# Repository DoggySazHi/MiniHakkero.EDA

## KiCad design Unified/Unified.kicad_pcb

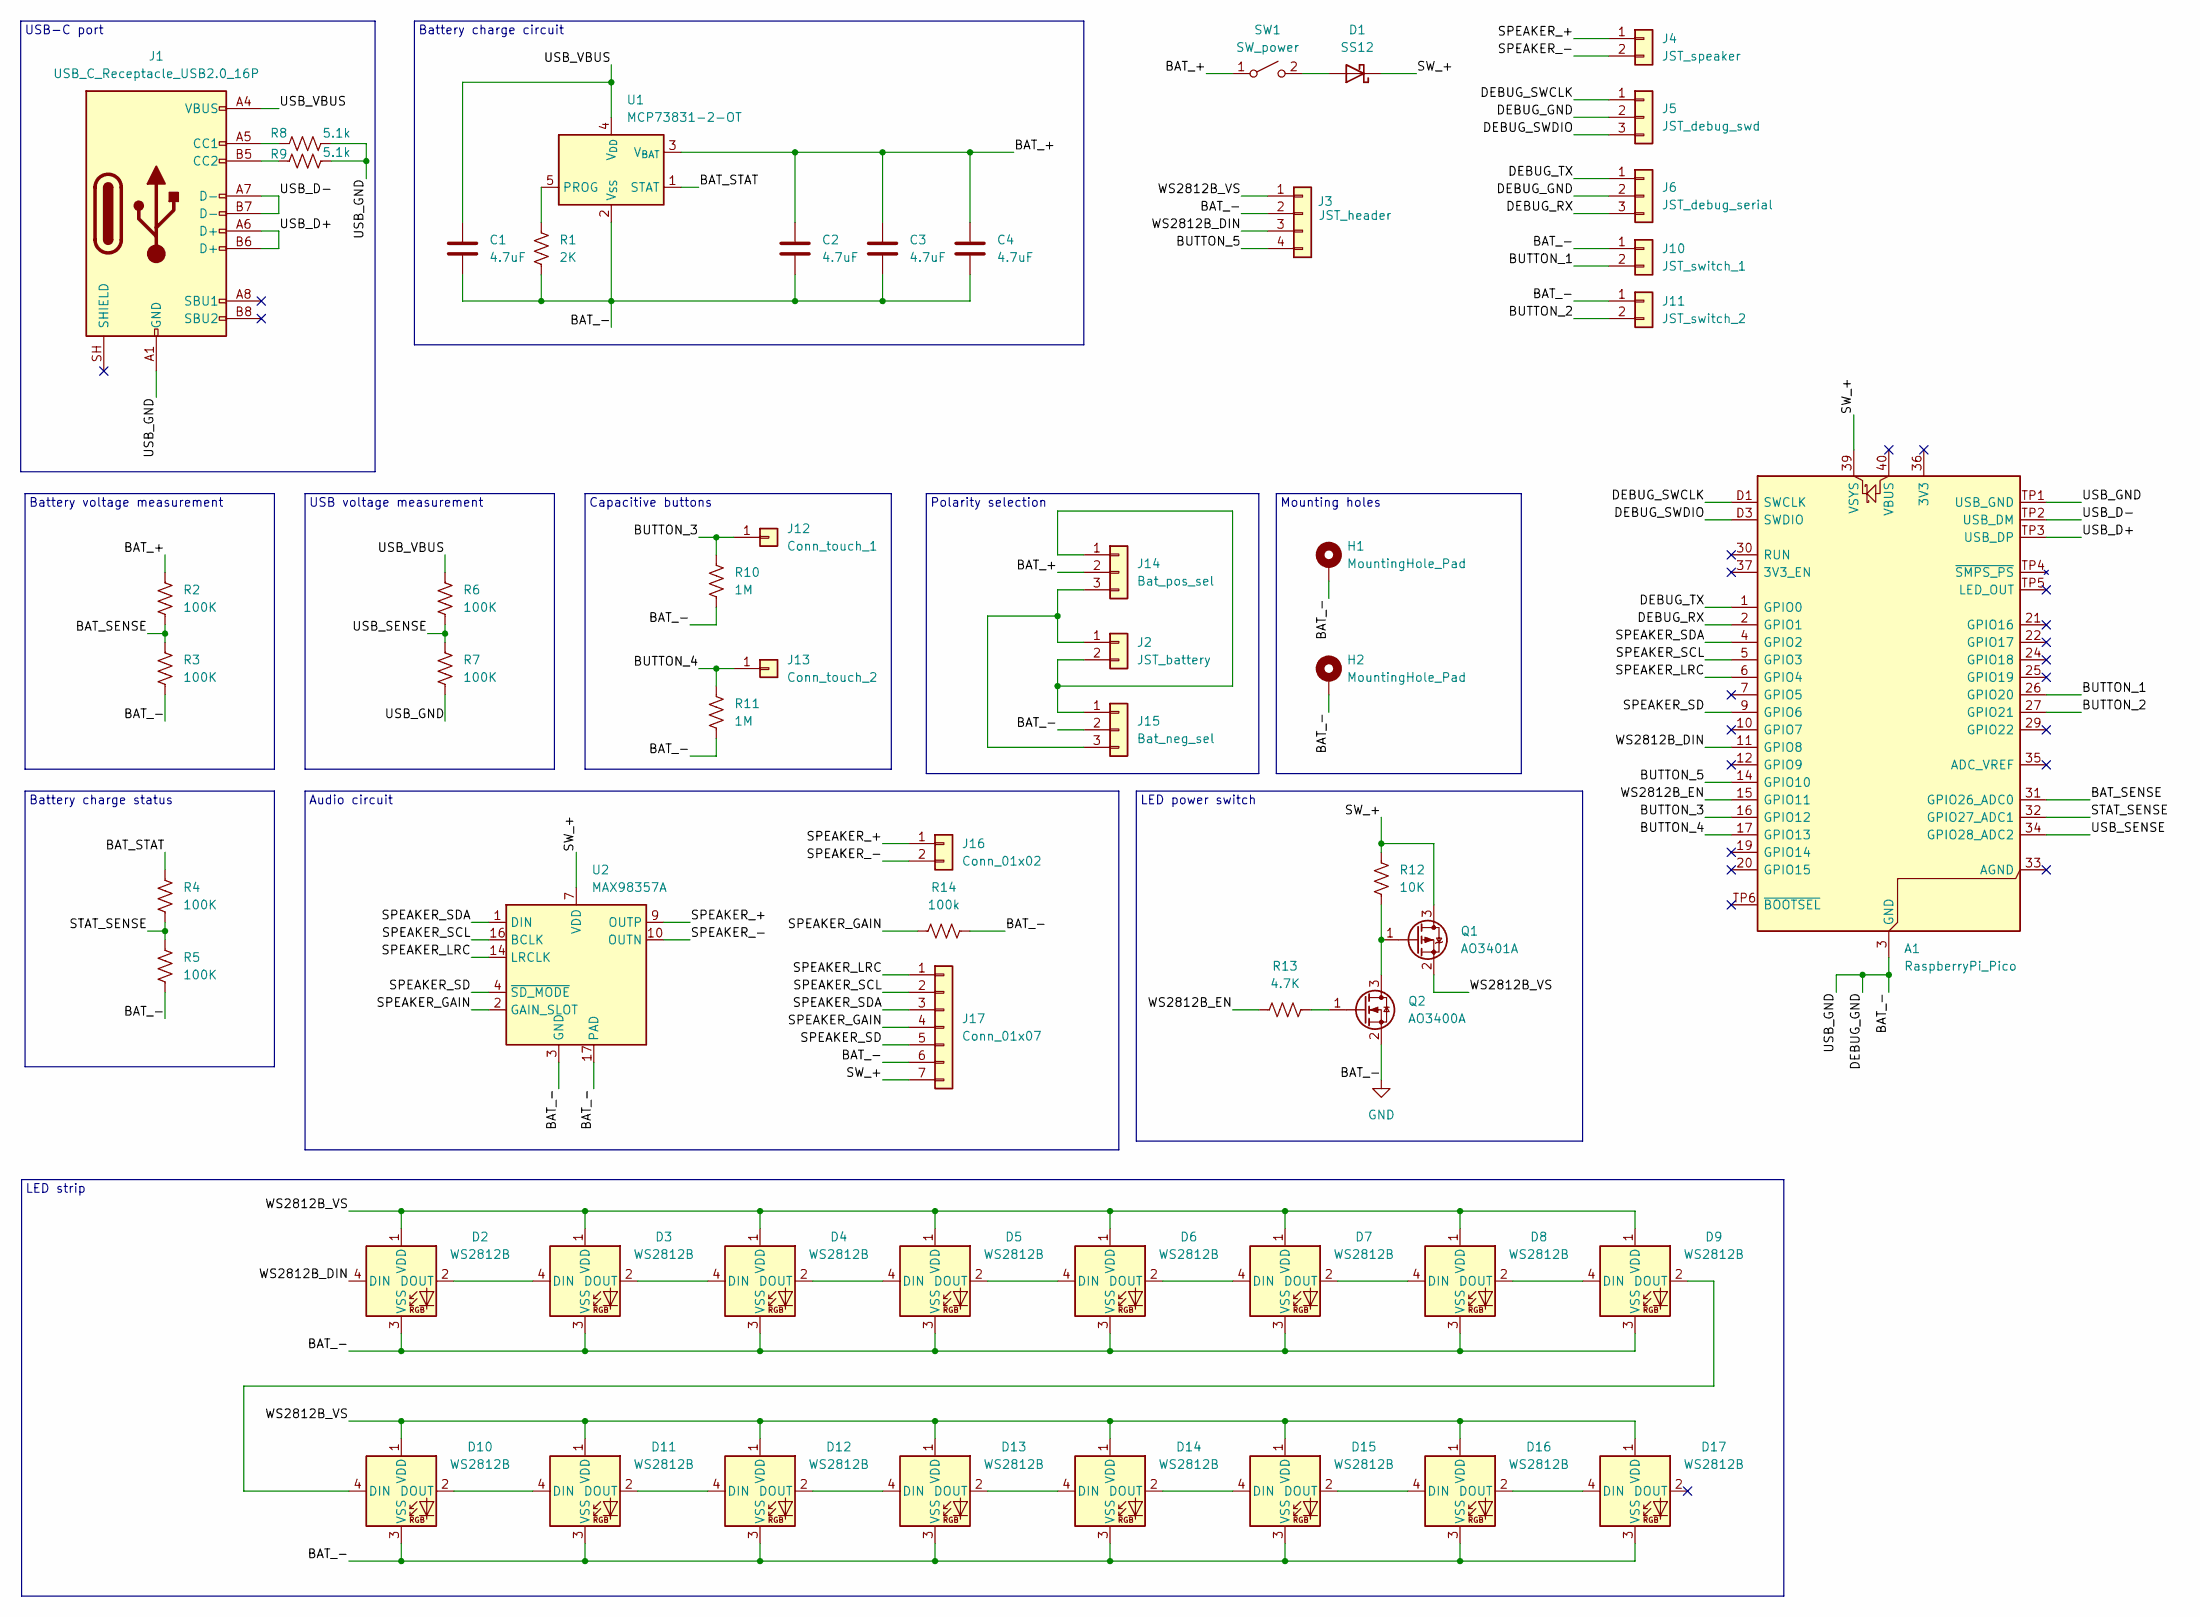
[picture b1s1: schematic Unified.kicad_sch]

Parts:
A1: RaspberryPi_Pico; RaspberryPi_Pico_SMD
C1, C2, C3, C4: 4.7uF; C_0603_1608Metric_Pad1.08x0.95mm_HandSolder
D1: SS12; D_SMA
D2, D3, D4, D5, D6, D7, D8, D9, D10, D11, D12, D13, D14, D15, D16, D17: WS2812B; LED_WS2812B_PLCC4_5.0x5.0mm_P3.2mm
H1, H2: MountingHole_Pad; MountingHole_2.2mm_M2_ISO7380_Pad
J1: USB_C_Receptacle_USB2.0_16P; USB_C_Receptacle_Palconn_UTC16-G
J2: JST_battery; JST_PH_B2B-PH-SM4-TB_1x02-1MP_P2.00mm_Vertical
J3: JST_header; JST_SH_BM04B-SRSS-TB_1x04-1MP_P1.00mm_Vertical
J4: JST_speaker; JST_SH_BM02B-SRSS-TB_1x02-1MP_P1.00mm_Vertical
J5: JST_debug_swd; JST_SH_BM03B-SRSS-TB_1x03-1MP_P1.00mm_Vertical
J6: JST_debug_serial; JST_SH_BM03B-SRSS-TB_1x03-1MP_P1.00mm_Vertical
J10: JST_switch_1; JST_SH_BM02B-SRSS-TB_1x02-1MP_P1.00mm_Vertical
J11: JST_switch_2; JST_SH_BM02B-SRSS-TB_1x02-1MP_P1.00mm_Vertical
J12: Conn_touch_1; PinHeader_1x01_P2.54mm_Vertical
J13: Conn_touch_2; PinHeader_1x01_P2.54mm_Vertical
J14: Bat_pos_sel; SolderJumper-3_P2.0mm_Open_TrianglePad1.0x1.5mm_NumberLabels
J15: Bat_neg_sel; SolderJumper-3_P2.0mm_Open_TrianglePad1.0x1.5mm_NumberLabels
J16: Conn_01x02; PinHeader_1x02_P2.54mm_Vertical
J17: Conn_01x07; PinSocket_1x07_P2.54mm_Vertical
Q1: AO3401A; SOT-23
Q2: AO3400A; SOT-23
R1: 2K; R_0603_1608Metric_Pad0.98x0.95mm_HandSolder
R2, R3, R4, R5, R6, R7: 100K; R_0603_1608Metric_Pad0.98x0.95mm_HandSolder
R8, R9: 5.1k; R_0603_1608Metric_Pad0.98x0.95mm_HandSolder
R10, R11: 1M; R_0603_1608Metric_Pad0.98x0.95mm_HandSolder
R12: 10K; R_0603_1608Metric_Pad0.98x0.95mm_HandSolder
R13: 4.7K; R_0603_1608Metric_Pad0.98x0.95mm_HandSolder
R14: 100k; R_0603_1608Metric_Pad0.98x0.95mm_HandSolder
SW1: SW_power; JST_SH_BM02B-SRSS-TB_1x02-1MP_P1.00mm_Vertical
U1: MCP73831-2-OT; SOT-23-5
U2: MAX98357A; TQFN-16-1EP_3x3mm_P0.5mm_EP1.23x1.23mm

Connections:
/BAT_+: C2.2, C3.2, C4.2, J14.2, R2.1, SW1.1 (A), U1.3 (V_{BAT})
/BAT_SENSE: A1.31 (GPIO26_ADC0), R2.2, R3.1
/BAT_STAT: R4.1, U1.1 (STAT)
/BUTTON_1: A1.26 (GPIO20), J10.2
/BUTTON_2: A1.27 (GPIO21), J11.2
/BUTTON_3: A1.16 (GPIO12), J12.1 (Pin_1_1), R10.1
/BUTTON_4: A1.17 (GPIO13), J13.1 (Pin_1_1), R11.1
/BUTTON_5: A1.14 (GPIO10), J3.4
/DEBUG_RX: A1.2 (GPIO1), J6.3
/DEBUG_SWCLK: A1.D1 (SWCLK), J5.1
/DEBUG_SWDIO: A1.D3 (SWDIO), J5.3
/DEBUG_TX: A1.1 (GPIO0), J6.1
/SPEAKER_+: J4.1, J16.1, U2.9 (OUTP)
/SPEAKER_-: J4.2, J16.2, U2.10 (OUTN)
/SPEAKER_GAIN: J17.4, R14.1, U2.2 (GAIN_SLOT)
/SPEAKER_LRC: A1.6 (GPIO4), J17.1, U2.14 (LRCLK)
/SPEAKER_SCL: A1.5 (GPIO3), J17.2, U2.16 (BCLK)
/SPEAKER_SD: A1.9 (GPIO6), J17.5, U2.4 (~SD_MODE)
/SPEAKER_SDA: A1.4 (GPIO2), J17.3, U2.1 (DIN)
/STAT_SENSE: A1.32 (GPIO27_ADC1), R4.2, R5.1
/SW_+: A1.39 (VSYS), D1.1 (K), J17.7, Q1.3 (D), R12.1, U2.7 (VDD), U2.8 (VDD)
/USB_D+: A1.TP3 (USB_DP), J1.A6 (D+), J1.B6 (D+)
/USB_D-: A1.TP2 (USB_DM), J1.A7 (D-), J1.B7 (D-)
/USB_SENSE: A1.34 (GPIO28_ADC2), R6.2, R7.1
/USB_VBUS: C1.2, J1.A4 (VBUS), J1.A9 (VBUS), J1.B4 (VBUS), J1.B9 (VBUS), R6.1, U1.4 (V_{DD})
/WS2812B_DIN: A1.11 (GPIO8), D2.4 (DIN), J3.3
/WS2812B_EN: A1.15 (GPIO11), R13.1
/WS2812B_VS: D2.1 (VDD), D3.1 (VDD), D4.1 (VDD), D5.1 (VDD), D6.1 (VDD), D7.1 (VDD), D8.1 (VDD), D9.1 (VDD), D10.1 (VDD), D11.1 (VDD), D12.1 (VDD), D13.1 (VDD), D14.1 (VDD), D15.1 (VDD), D16.1 (VDD), D17.1 (VDD), J3.1, Q1.2 (S)
GND: A1.3 (GND), A1.8 (GND), A1.13 (GND), A1.18 (GND), A1.23 (GND), A1.28 (GND), A1.38 (GND), A1.D2 (GND), A1.TP1 (USB_GND), C1.1, C2.1, C3.1, C4.1, D2.3 (VSS), D3.3 (VSS), D4.3 (VSS), D5.3 (VSS), D6.3 (VSS), D7.3 (VSS), D8.3 (VSS), D9.3 (VSS), D10.3 (VSS), D11.3 (VSS), D12.3 (VSS), D13.3 (VSS), D14.3 (VSS), D15.3 (VSS), D16.3 (VSS), D17.3 (VSS), H1.1 (1_1), H2.1 (1_1), J1.A1 (GND), J1.A12 (GND), J1.B1 (GND), J1.B12 (GND), J3.2, J5.2, J6.2, J10.1, J11.1, J15.2, J17.6, Q2.2 (S), R1.2, R3.2, R5.2, R7.2, R8.2, R9.2, R10.2, R11.2, R14.2, U1.2 (V_{SS}), U2.3 (GND), U2.11 (GND), U2.15 (GND), U2.17 (PAD)
unnamed: D1.2 (A), SW1.2 (B)
unnamed: D2.2 (DOUT), D3.4 (DIN)
unnamed: D3.2 (DOUT), D4.4 (DIN)
unnamed: D4.2 (DOUT), D5.4 (DIN)
unnamed: D5.2 (DOUT), D6.4 (DIN)
unnamed: D6.2 (DOUT), D7.4 (DIN)
unnamed: D7.2 (DOUT), D8.4 (DIN)
unnamed: D8.2 (DOUT), D9.4 (DIN)
unnamed: D9.2 (DOUT), D10.4 (DIN)
unnamed: D10.2 (DOUT), D11.4 (DIN)
unnamed: D11.2 (DOUT), D12.4 (DIN)
unnamed: D12.2 (DOUT), D13.4 (DIN)
unnamed: D13.2 (DOUT), D14.4 (DIN)
unnamed: D14.2 (DOUT), D15.4 (DIN)
unnamed: D15.2 (DOUT), D16.4 (DIN)
unnamed: D16.2 (DOUT), D17.4 (DIN)
unnamed: J1.A5 (CC1), R8.1
unnamed: J1.B5 (CC2), R9.1
unnamed: J2.2, J14.1, J15.1
unnamed: J2.1, J14.3, J15.3
unnamed: Q1.1 (G), Q2.3 (D), R12.2
unnamed: Q2.1 (G), R13.2
unnamed: R1.1, U1.5 (PROG)

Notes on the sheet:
Battery voltage measurement
USB voltage measurement
USB-C port
Polarity selection
LED strip
Mounting holes
Battery charge circuit
Audio circuit
Capacitive buttons
LED power switch
Battery charge status

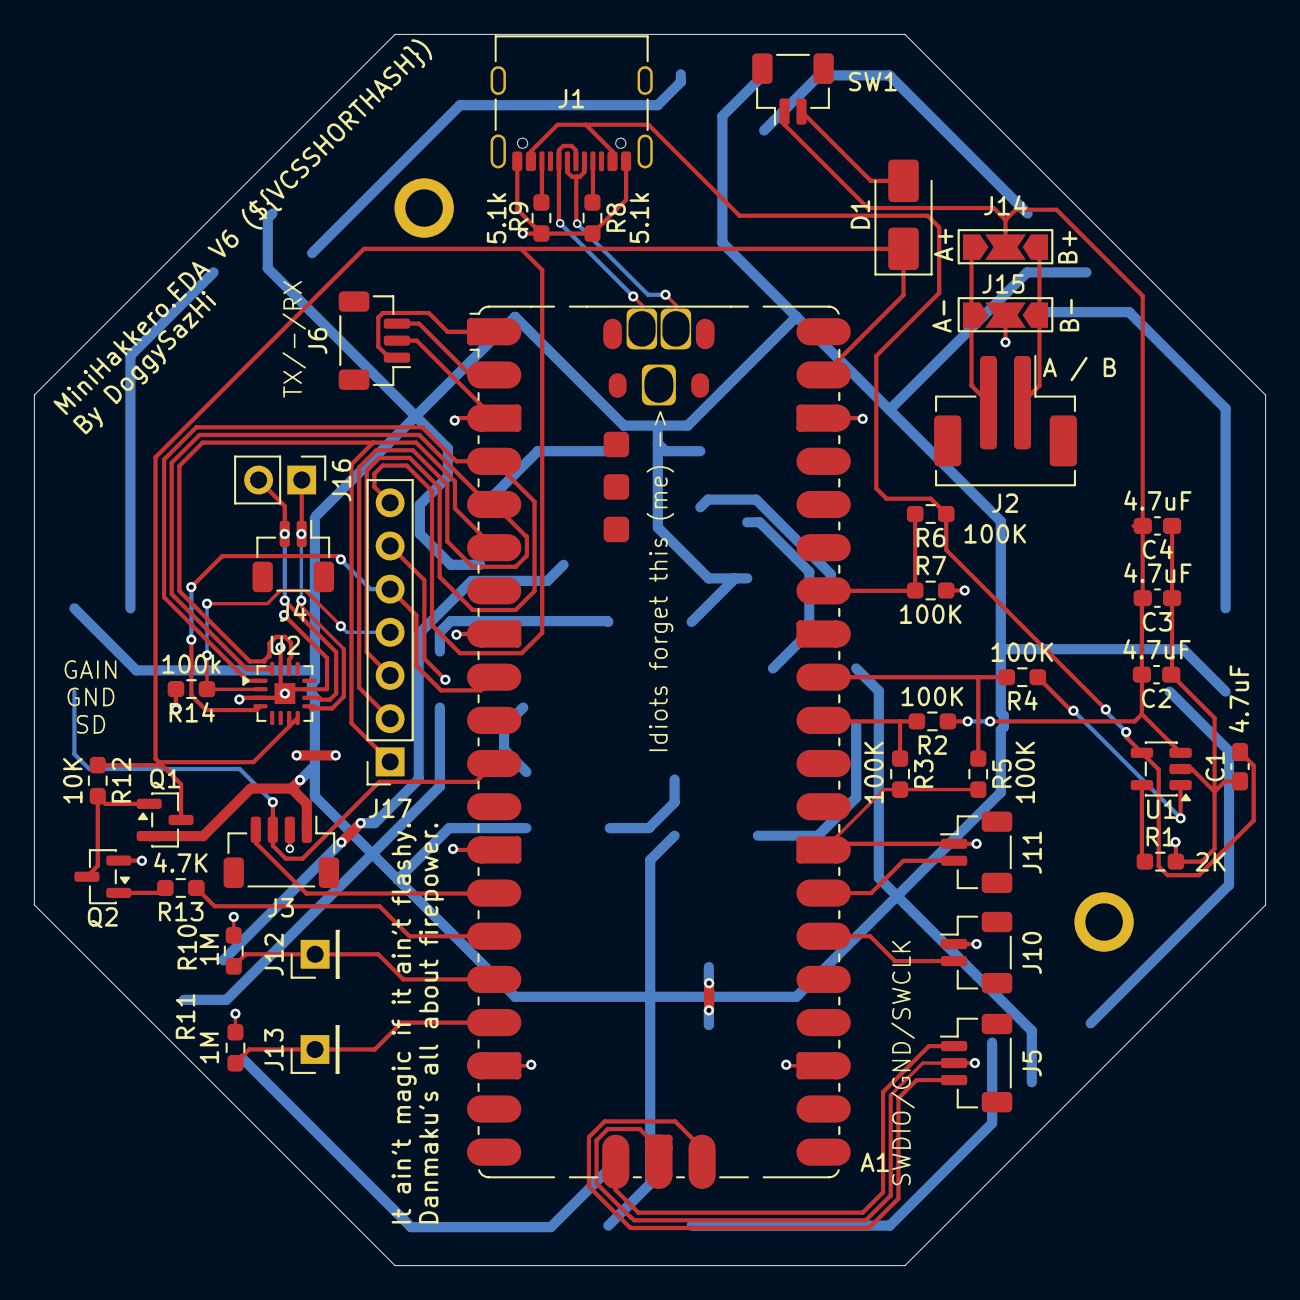
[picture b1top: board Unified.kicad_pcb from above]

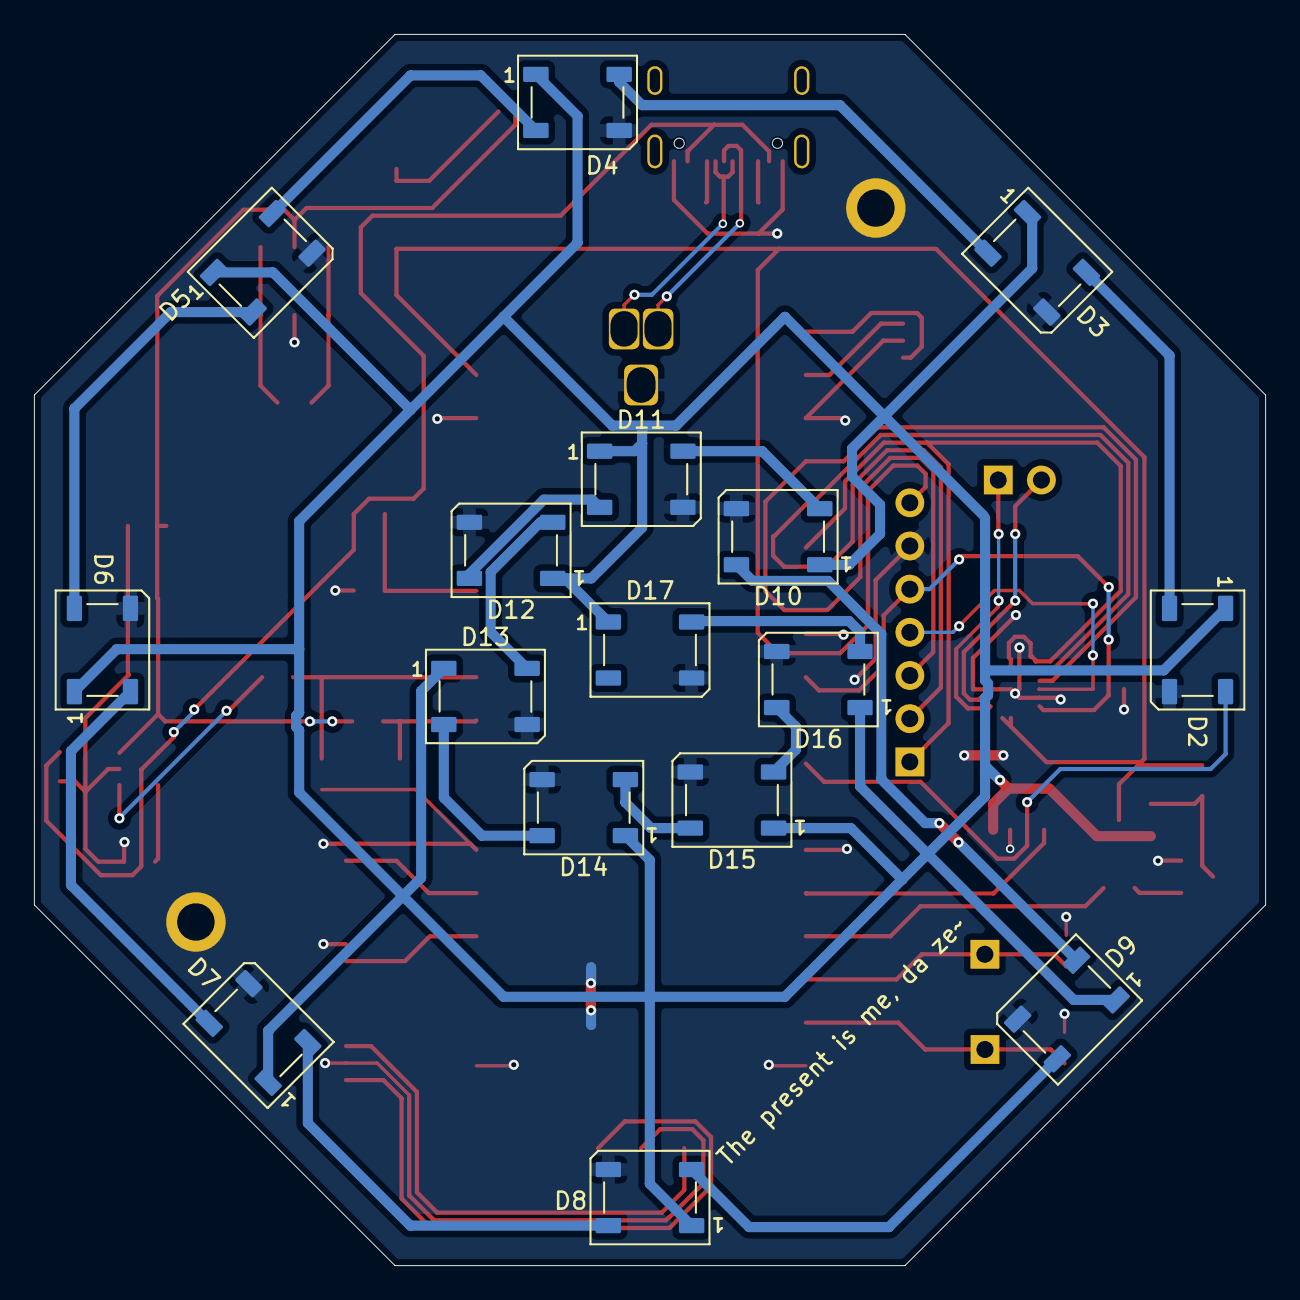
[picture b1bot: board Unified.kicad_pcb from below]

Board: 2 copper layers, 72.4 x 72.4 mm, 57 parts (16 on the bottom side), 52 nets.
